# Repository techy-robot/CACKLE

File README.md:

---
modified: 2025-11-08T10:36:11-07:00
---
# CACKLE - Card Adaptable Controller Kinetic Link Electronics

This is designed to be a super small, open source, adaptable control board. Each module is arranged in units of 1.5cm squared, but can handle high power micro robotic actuators, such as my [Mighty-Micro-Motors](https://github.com/techy-robot/Mighty-Micro-Motors). Ideally this board can be reused and rebuilt for all sorts of small robots.

You can read up on specific modules in their respective git sub modules in Hardware, or take a look at the overall architecture

Real Life pictures:

3D model demo:

# Architecture
There are currently 6 types of sub-boards:
- Hubs (with a MCU on it, supports 2 or 4 drivers, 2 expansion cards, and a chain of peers)
- PSUs (typically only one board)
- Expansion Cards (vertical mezzanine connector boards for breaking out sensors and other interfaces)
- Drivers (Any high power driver)
- nanoSPI devices (Small 7-pin flex cable SPI devices, mostly for sensors)
- Passives (spacers, end caps, etc...)

The base unit for this project is 1.5 cm squared. The expansion cards and drivers should each be 1 unit, the Hubs 1x1 or 1x2, and the PSUs 3x1 units. For example, with a 12 motor board you would need 1 PSU, 3 1-by-2 hubs, and 12 drivers; the board would be 45x105mm. nanoSPI devices can be much smaller due to the  2.4mm wide flex cable, such as a 5mm diameter magnetic encoder.

Unfortunately I was unable to create a 45x15mm PSU for the first version, it had to be extended up by 5mm to fit the high current circuitry.

My initial idea was to have spring contacts to allow easy clip in clip out, but finding no connectors quite what I wanted and unable to manufacture my own, I went with 1.27mm pitch pin headers and micro Keystone edge board connectors for power.

Original (bit outdated) sketch of the architecture:

# Goals
- Adaptable 
- Small
- Extendable by other developers
- Easy to use
- Powerful

# Features
## Required:
- Super Small modules
- Hubs with an mcu that can talk to its peers and a master
- Motor driver boards that can handle several amps
- Sensor ports with protocols like i2c and SPI
- Extendable architecture
- PSUs
- LED status lights

## Nice to Have
- Distributed computing with a multi-master network
- Easy automatic hardware configuration
- Ability to stack hubs vertically using the Expansion Card system, in addition to horizontal chaining.

# Software
As of now software is very limited in scope, I have not had the time to fully assembly and test the boards I have made. I am planning on using SimpleFOC and Luos Engine. SimpleFOC is a motor driver library for Field Oreinted Control for motors. Luos Engine is a lightweight-distributed communication engine that aims to make hardware as modular as software. Combined, I have covered 50% of the use-cases of the code necessary for this project.

See [Software](Software/README.md) for more.

# Contributing
Feal free to contribute in any way possible! This is an open-source project, and with so many modules yet to be explored, I encourage you to help test boards, create modules or code, or ask about the project!

- GitHub Discussions: Participate in discussions on GitHub to share your experiences and ask questions.
- Contribute: Help develop the project, create PRs with new features or modules
- Report: Open issues, give me feedback!

Read the Architecture notes and [CONTRIBUTING.md](CONTRIBUTING.md) for more in-depth on this.

# A Note on Project Management
I am using Obsidian.md as my notetaking and documentation tool. A lot of the markdown files you will see in this repo might look a bit weird; that is due to the YAML file front-matter that Obsidian supports, and occasional plugins with custom code.

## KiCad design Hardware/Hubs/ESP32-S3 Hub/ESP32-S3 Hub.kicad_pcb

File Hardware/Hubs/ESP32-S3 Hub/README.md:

---
modified: 2025-01-12T16:18:18-07:00
---

# ESP32-S3 Hub

This is a 4-driver hub based on the Espressif ESP32-S3FH4 chip. It has two cores powerful running at 240 mhz, and 4mb of flash memory. Other variants of the ESP32-S3 can be used as long as they have built in flash memory.

The ESP32-S3 chip does not *quite* have enough pins for driving 4 motors and several sensors, so some cuts were made. For example, on all 4 ports for the ADCs, only two out of three pins are actually connected. This will work for brushed and brushless FOC control, but it may not work for other use cases. I also had to use the USB lines for a tri-state shift register, which controls all the SPI chip select lines. I am planning on programming the chip via UART, which means that the RS485 lines must be disconnected.

The SPI bus should be able to operate at 80mhz, though this has not been tested yet. For all practical use-cases I am limiting this to 20mhz.

Partial 3D picture (headers not shown)

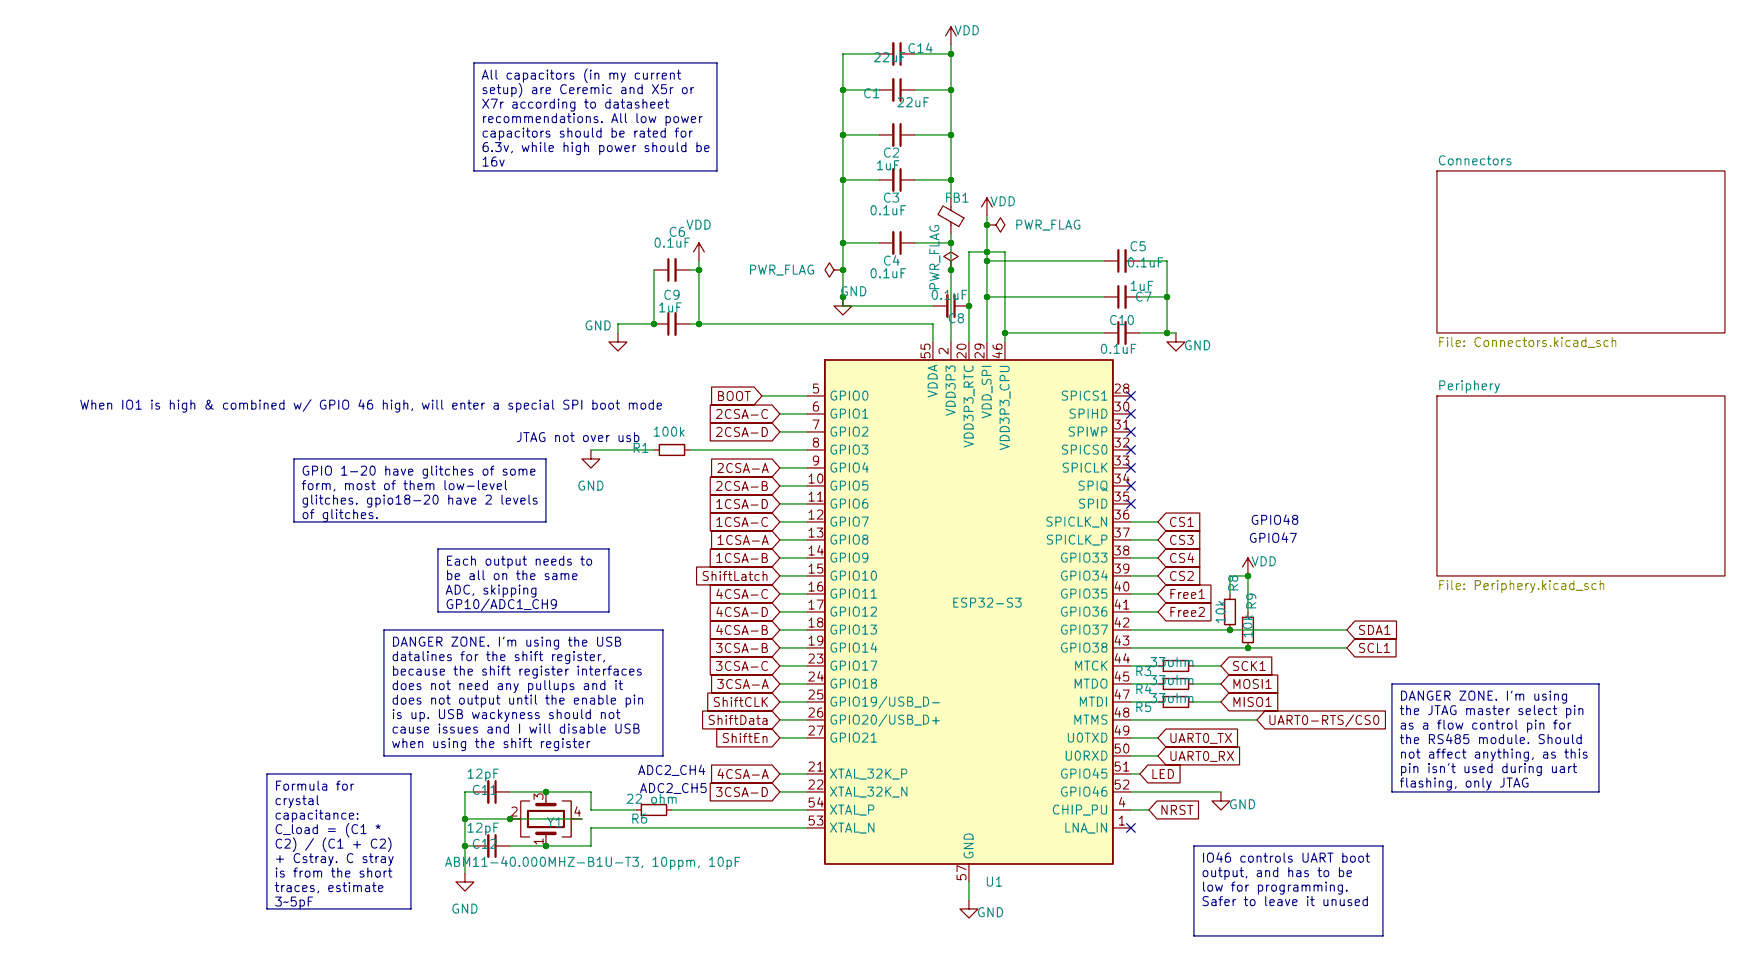
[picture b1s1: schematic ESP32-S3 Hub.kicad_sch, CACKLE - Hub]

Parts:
C1, C14: 22uF; C_0402_1005Metric; LCSC C415703
C2, C7, C9: 1uF; C_0402_1005Metric; LCSC C52923
C3, C4, C5, C6, C8, C10: 0.1uF; C_0402_1005Metric; LCSC C1525
C11, C12: 12pF; C_0402_1005Metric; LCSC C1547
FB1: 120ohm imp @100mhz, 1 amp; L_0402_1005Metric; LCSC C82861
R1: 100k; R_0402_1005Metric; LCSC C25741
R3, R4, R5: 33ohm; R_0402_1005Metric; LCSC C25105
R6: 22 ohm; R_0402_1005Metric; LCSC C25092
R8, R9: 10k; R_0402_1005Metric; LCSC C25744
U1: ESP32-S3; QFN-56-1EP_7x7mm_P0.4mm_EP4x4mm; LCSC C3013940
Y1: ABM11-40.000MHZ-B1U-T3, 10ppm, 10pF; Crystal_SMD_2016-4Pin_2.0x1.6mm; LCSC C648973

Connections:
1CSA-A: U1.13 (GPIO8); also elsewhere on the board
1CSA-B: U1.14 (GPIO9); also elsewhere on the board
1CSA-C: U1.12 (GPIO7); also elsewhere on the board
1CSA-D: U1.11 (GPIO6); also elsewhere on the board
2CSA-A: U1.9 (GPIO4); also elsewhere on the board
2CSA-B: U1.10 (GPIO5); also elsewhere on the board
2CSA-C: U1.6 (GPIO1); also elsewhere on the board
2CSA-D: U1.7 (GPIO2); also elsewhere on the board
3CSA-A: U1.24 (GPIO18); also elsewhere on the board
3CSA-B: U1.19 (GPIO14); also elsewhere on the board
3CSA-C: U1.23 (GPIO17); also elsewhere on the board
3CSA-D: U1.22 (XTAL_32K_N); also elsewhere on the board
4CSA-A: U1.21 (XTAL_32K_P); also elsewhere on the board
4CSA-B: U1.18 (GPIO13); also elsewhere on the board
4CSA-C: U1.16 (GPIO11); also elsewhere on the board
4CSA-D: U1.17 (GPIO12); also elsewhere on the board
BOOT: U1.5 (GPIO0); also elsewhere on the board
CS1: U1.36 (SPICLK_N); also elsewhere on the board
CS2: U1.39 (GPIO34); also elsewhere on the board
CS3: U1.37 (SPICLK_P); also elsewhere on the board
CS4: U1.38 (GPIO33); also elsewhere on the board
Free1: U1.40 (GPIO35); also elsewhere on the board
Free2: U1.41 (GPIO36); also elsewhere on the board
GND: C1.2, C2.2, C3.2, C4.2, C5.2, C6.1, C7.2, C8.2, C9.1, C10.2, C11.2, C12.2, C14.2, R1.2, U1.52 (GPIO46), U1.57 (GND), Y1.2, Y1.4; also elsewhere on the board
LED: U1.51 (GPIO45); also elsewhere on the board
MISO1: R5.2; also elsewhere on the board
MOSI1: R4.2; also elsewhere on the board
NRST: U1.4 (CHIP_PU); also elsewhere on the board
unnamed: C4.1, FB1.1, U1.2 (VDD3P3), U1.3 (VDD3P3)
unnamed: C11.1, R6.1, Y1.3
unnamed: R1.1, U1.8 (GPIO3)
unnamed: R3.1, U1.44 (MTCK)
unnamed: R5.1, U1.47 (MTDI)
unnamed: R4.1, U1.45 (MTDO)
unnamed: C12.1, U1.53 (XTAL_N), Y1.1
unnamed: R6.2, U1.54 (XTAL_P)
SCK1: R3.2; also elsewhere on the board
SCL1: R9.2, U1.43 (GPIO38); also elsewhere on the board
SDA1: R8.2, U1.42 (GPIO37); also elsewhere on the board
ShiftCLK: U1.25 (GPIO19/USB_D-); also elsewhere on the board
ShiftData: U1.26 (GPIO20/USB_D+); also elsewhere on the board
ShiftEn: U1.27 (GPIO21); also elsewhere on the board
ShiftLatch: U1.15 (GPIO10); also elsewhere on the board
UART0-RTS/CS0: U1.48 (MTMS); also elsewhere on the board
UART0_RX: U1.50 (U0RXD); also elsewhere on the board
UART0_TX: U1.49 (U0TXD); also elsewhere on the board
VDD: C1.1, C2.1, C3.1, C5.1, C6.2, C7.1, C8.1, C9.2, C10.1, C14.1, FB1.2, R8.1, R9.1, U1.20 (VDD3P3_RTC), U1.29 (VDD_SPI), U1.46 (VDD3P3_CPU), U1.55 (VDDA), U1.56 (VDDA); also elsewhere on the board

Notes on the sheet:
GPIO48
JTAG not over usb
GPIO47
When IO1 is high & combined w/ GPIO 46 high, will enter a special SPI boot mode
ADC2_CH4
ADC2_CH5
DANGER ZONE. I'm using the JTAG master select pin as a flow control pin for the RS485 module. Should not affect anything, as this pin isn't used during uart flashing, only JTAG
DANGER ZONE. I'm using the USB datalines for the shift register, because the shift register interfaces does not need any pullups and it does not output until the enable pin is up. USB wackyness should not cause issues and I will disable USB when using the shift register
All capacitors (in my current setup) are Ceremic and X5r or X7r according to datasheet recommendations. All low power capacitors should be rated for 6.3v, while high power should be 16v
IO46 controls UART boot output, and has to be low for programming. Safer to leave it unused
Each output needs to be all on the same ADC, skipping GP10/ADC1_CH9
GPIO 1-20 have glitches of some form, most of them low-level glitches. gpio18-20 have 2 levels of glitches.
Formula for crystal capacitance: C_load = (C1 * C2) / (C1 + C2) + Cstray. C stray is from the short traces, estimate 3~5pF

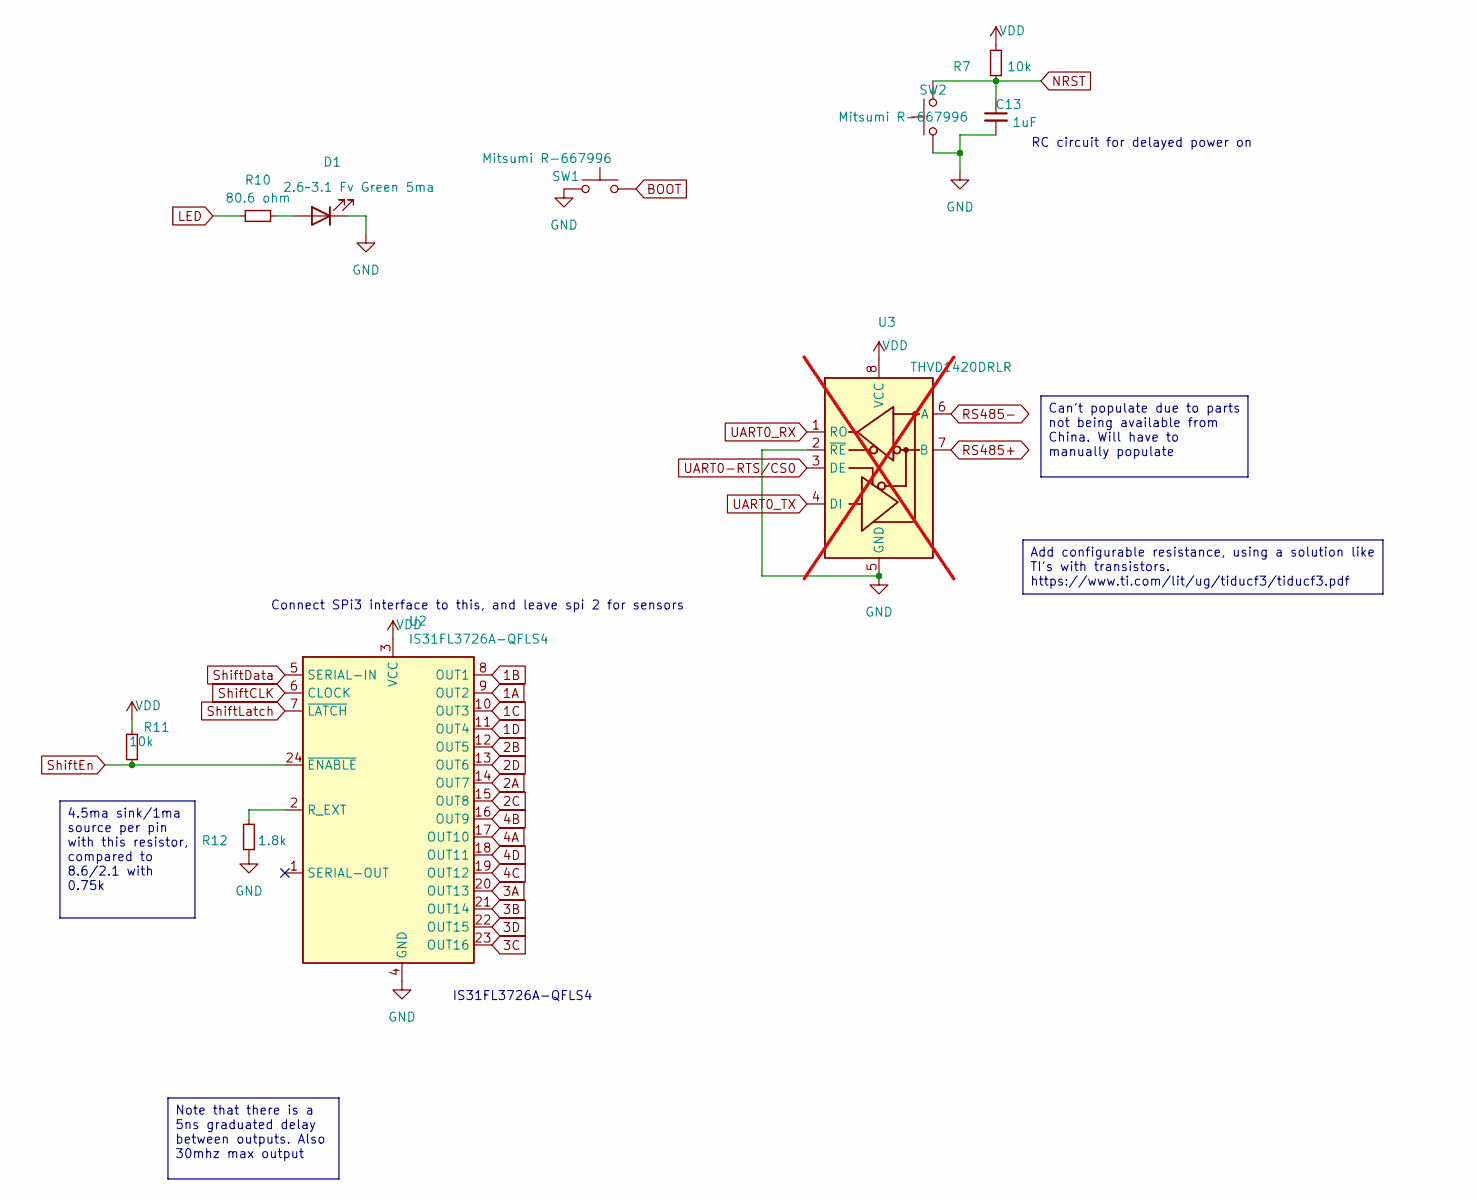
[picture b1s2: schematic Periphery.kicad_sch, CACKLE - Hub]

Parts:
C13: 1uF; C_0402_1005Metric; LCSC C52923
D1: 2.6~3.1 Fv Green 5ma; LED_0603_1608Metric_Pad1.05x0.95mm_HandSolder; LCSC C3028858
R7, R11: 10k; R_0402_1005Metric; LCSC C25744
R10: 80.6 ohm; R_0402_1005Metric; LCSC C185392
R12: 1.8k; R_0402_1005Metric; LCSC C25744
SW1, SW2: Mitsumi R-667996; R-667995_MIT; LCSC C4365007
U2: IS31FL3726A-QFLS4; QFN-24-1EP_4x4mm_P0.5mm_EP2.7x2.7mm
U3: THVD1420DRLR; SOT-583-8; not fitted

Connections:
1A: U2.9 (OUT2); also elsewhere on the board
1B: U2.8 (OUT1); also elsewhere on the board
1C: U2.10 (OUT3); also elsewhere on the board
1D: U2.11 (OUT4); also elsewhere on the board
2A: U2.14 (OUT7); also elsewhere on the board
2B: U2.12 (OUT5); also elsewhere on the board
2C: U2.15 (OUT8); also elsewhere on the board
2D: U2.13 (OUT6); also elsewhere on the board
3A: U2.20 (OUT13); also elsewhere on the board
3B: U2.21 (OUT14); also elsewhere on the board
3C: U2.23 (OUT16); also elsewhere on the board
3D: U2.22 (OUT15); also elsewhere on the board
4A: U2.17 (OUT10); also elsewhere on the board
4B: U2.16 (OUT9); also elsewhere on the board
4C: U2.19 (OUT12); also elsewhere on the board
4D: U2.18 (OUT11); also elsewhere on the board
BOOT: SW1.2; also elsewhere on the board
GND: C13.2, D1.1 (K), R12.1, SW1.1, SW2.1, U2.4 (GND), U2.25 (GND), U3.2 (~RE), U3.5 (GND); also elsewhere on the board
LED: R10.1; also elsewhere on the board
NRST: C13.1, R7.1, SW2.2; also elsewhere on the board
unnamed: D1.2 (A), R10.2
unnamed: R12.2, U2.2 (R_EXT)
RS485+: U3.7 (B); also elsewhere on the board
RS485-: U3.6 (A); also elsewhere on the board
ShiftCLK: U2.6 (CLOCK); also elsewhere on the board
ShiftData: U2.5 (SERIAL-IN); also elsewhere on the board
ShiftEn: R11.1, U2.24 (~ENABLE); also elsewhere on the board
ShiftLatch: U2.7 (~LATCH); also elsewhere on the board
UART0-RTS/CS0: U3.3 (DE); also elsewhere on the board
UART0_RX: U3.1 (RO); also elsewhere on the board
UART0_TX: U3.4 (DI); also elsewhere on the board
VDD: R7.2, R11.2, U2.3 (VCC), U3.8 (VCC); also elsewhere on the board

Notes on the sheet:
IS31FL3726A-QFLS4
RC circuit for delayed power on
Connect SPi3 interface to this, and leave spi 2 for sensors
Can't populate due to parts not being available from China. Will have to manually populate
Add configurable resistance, using a solution like TI's with transistors. https://www.ti.com/lit/ug/tiducf3/tiducf3.pdf
Note that there is a 5ns graduated delay between outputs. Also 30mhz max output
4.5ma sink/1ma source per pin with this resistor, compared to 8.6/2.1 with 0.75k

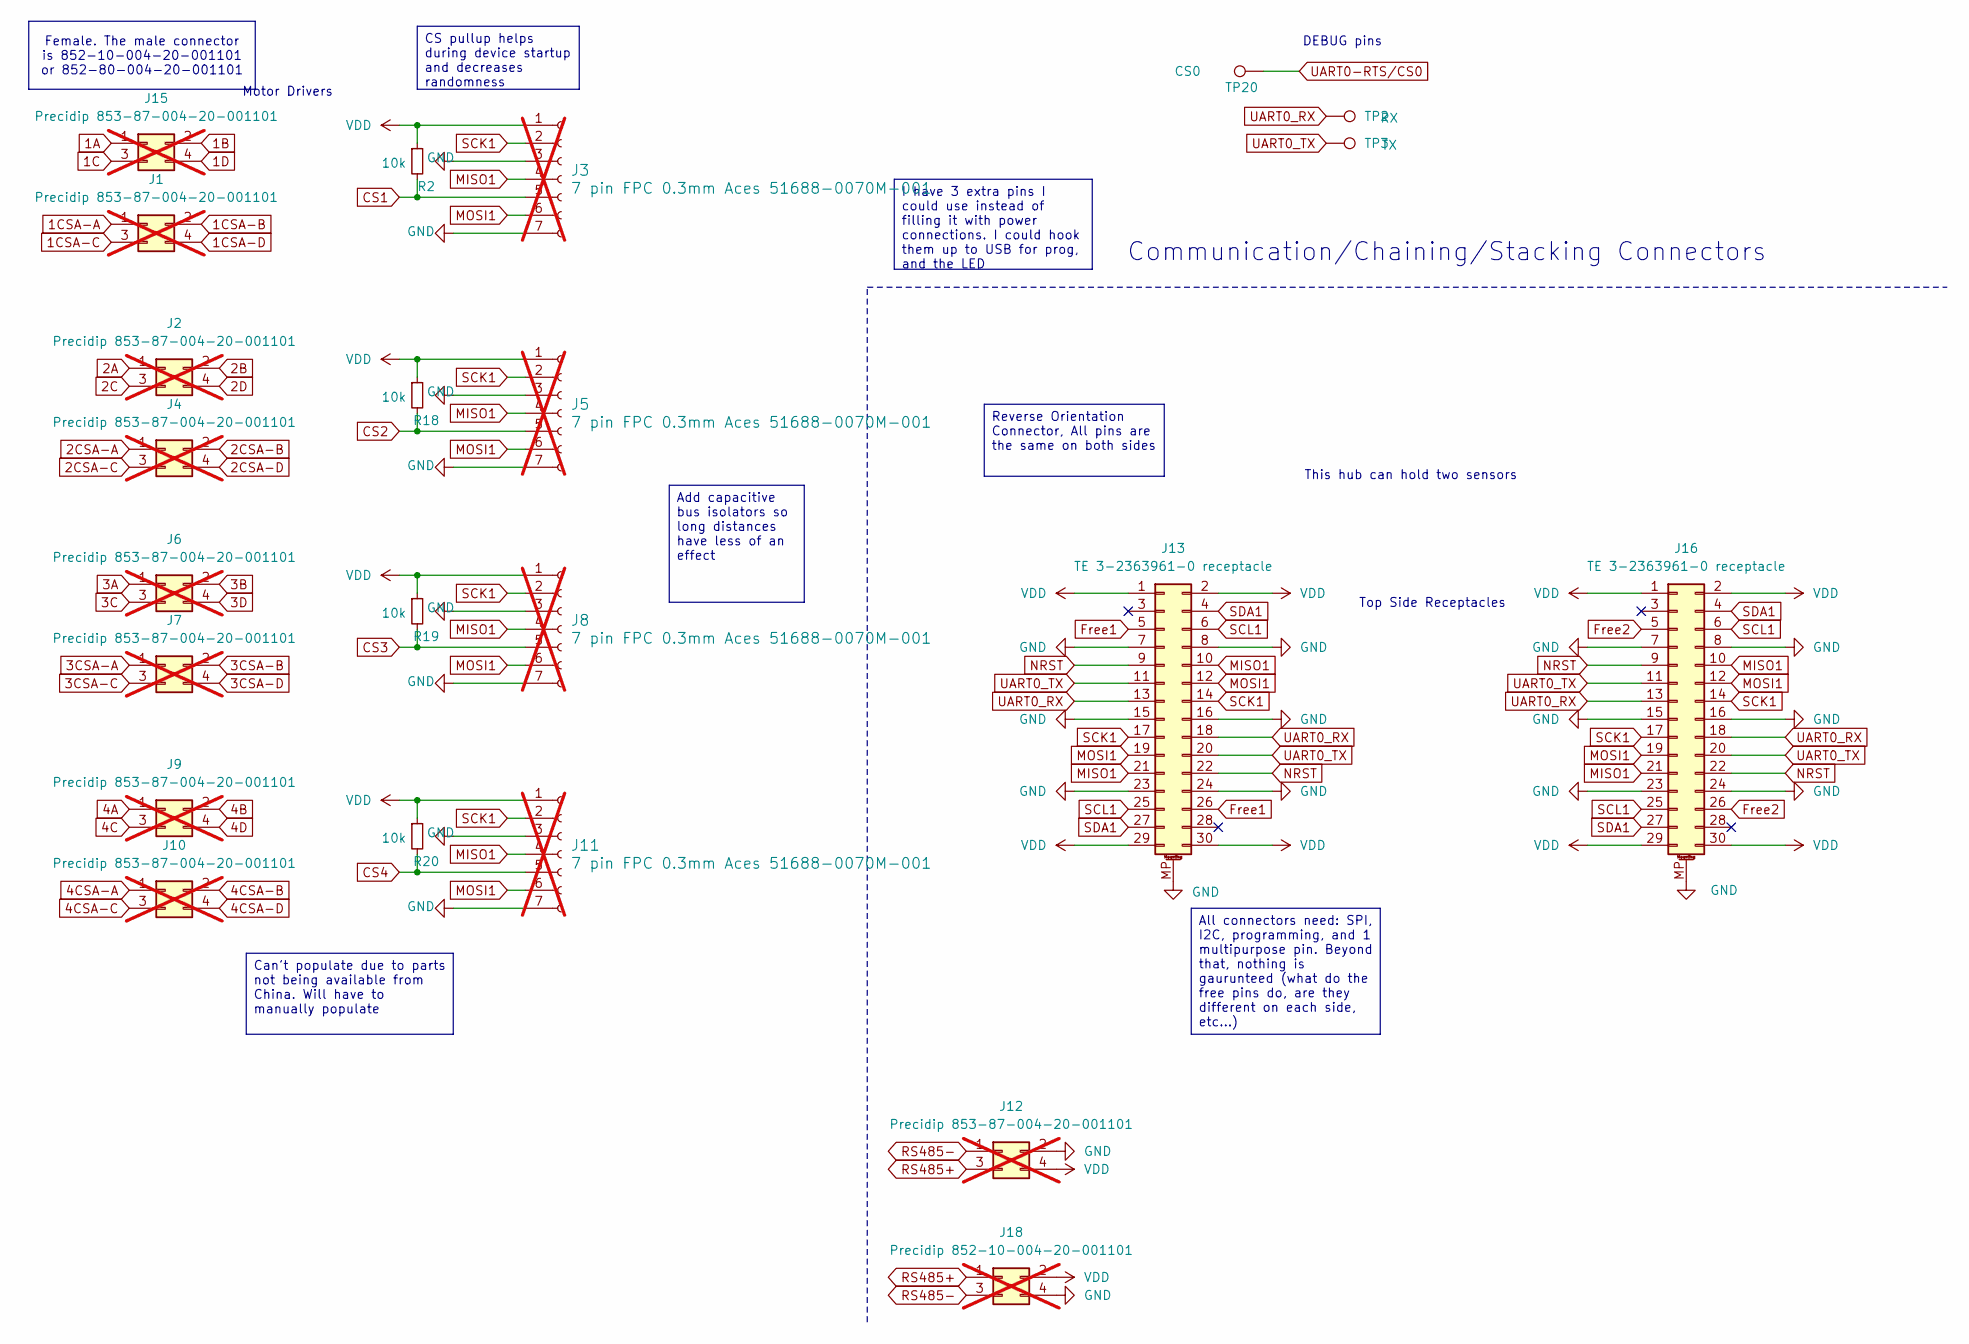
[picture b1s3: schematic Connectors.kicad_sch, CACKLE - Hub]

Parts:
J1, J2, J4, J6, J7, J9, J10, J12, J15: Precidip 853-87-004-20-001101; PinHeader_2x02_P1.27mm_Horizontal; not fitted
J3, J5, J8, J11: 7 pin FPC 0.3mm Aces 51688-0070M-001; fpc_7pin_0.3mm_connector Aces; not fitted
J13, J16: TE 3-2363961-0 receptacle; TE_mezzanine_rec_3-2363961-0; LCSC C425103
J18: Precidip 852-10-004-20-001101; PinHeader_2x02_P1.27mm_Horizontal; not fitted
R2, R18, R19, R20: 10k; R_0402_1005Metric; LCSC C25744
TP2: RX; TestPoint_Pad_D1.0mm
TP3: TX; TestPoint_Pad_D1.0mm
TP20: CS0; TestPoint_Pad_D1.0mm

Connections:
1A: J15.1; also elsewhere on the board
1B: J15.2; also elsewhere on the board
1C: J15.3; also elsewhere on the board
1CSA-A: J1.1; also elsewhere on the board
1CSA-B: J1.2; also elsewhere on the board
1CSA-C: J1.3; also elsewhere on the board
1CSA-D: J1.4; also elsewhere on the board
1D: J15.4; also elsewhere on the board
2A: J2.1; also elsewhere on the board
2B: J2.2; also elsewhere on the board
2C: J2.3; also elsewhere on the board
2CSA-A: J4.1; also elsewhere on the board
2CSA-B: J4.2; also elsewhere on the board
2CSA-C: J4.3; also elsewhere on the board
2CSA-D: J4.4; also elsewhere on the board
2D: J2.4; also elsewhere on the board
3A: J6.1; also elsewhere on the board
3B: J6.2; also elsewhere on the board
3C: J6.3; also elsewhere on the board
3CSA-A: J7.1; also elsewhere on the board
3CSA-B: J7.2; also elsewhere on the board
3CSA-C: J7.3; also elsewhere on the board
3CSA-D: J7.4; also elsewhere on the board
3D: J6.4; also elsewhere on the board
4A: J9.1; also elsewhere on the board
4B: J9.2; also elsewhere on the board
4C: J9.3; also elsewhere on the board
4CSA-A: J10.1; also elsewhere on the board
4CSA-B: J10.2; also elsewhere on the board
4CSA-C: J10.3; also elsewhere on the board
4CSA-D: J10.4; also elsewhere on the board
4D: J9.4; also elsewhere on the board
CS1: J3.5, R2.2; also elsewhere on the board
CS2: J5.5, R18.2; also elsewhere on the board
CS3: J8.5, R19.2; also elsewhere on the board
CS4: J11.5, R20.2; also elsewhere on the board
Free1: J13.5, J13.26; also elsewhere on the board
Free2: J16.5, J16.26; also elsewhere on the board
GND: J3.3, J3.7, J5.3, J5.7, J8.3, J8.7, J11.3, J11.7, J12.2, J13.7, J13.8, J13.15, J13.16, J13.23, J13.24, J13.MP (MountPin), J16.7, J16.8, J16.15, J16.16, J16.23, J16.24, J16.MP (MountPin), J18.4; also elsewhere on the board
MISO1: J3.4, J5.4, J8.4, J11.4, J13.10, J13.21, J16.10, J16.21; also elsewhere on the board
MOSI1: J3.6, J5.6, J8.6, J11.6, J13.12, J13.19, J16.12, J16.19; also elsewhere on the board
NRST: J13.9, J13.22, J16.9, J16.22; also elsewhere on the board
RS485+: J12.3, J18.1; also elsewhere on the board
RS485-: J12.1, J18.3; also elsewhere on the board
SCK1: J3.2, J5.2, J8.2, J11.2, J13.14, J13.17, J16.14, J16.17; also elsewhere on the board
SCL1: J13.6, J13.25, J16.6, J16.25; also elsewhere on the board
SDA1: J13.4, J13.27, J16.4, J16.27; also elsewhere on the board
UART0-RTS/CS0: TP20.1; also elsewhere on the board
UART0_RX: J13.13, J13.18, J16.13, J16.18, TP2.1; also elsewhere on the board
UART0_TX: J13.11, J13.20, J16.11, J16.20, TP3.1; also elsewhere on the board
VDD: J3.1, J5.1, J8.1, J11.1, J12.4, J13.1, J13.2, J13.29, J13.30, J16.1, J16.2, J16.29, J16.30, J18.2, R2.1, R18.1, R19.1, R20.1; also elsewhere on the board

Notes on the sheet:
Communication/Chaining/Stacking Connectors
Top Side Receptacles
Motor Drivers
This hub can hold two sensors
DEBUG pins
Reverse Orientation Connector, All pins are the same on both sides
CS pullup helps during device startup and decreases randomness
Can't populate due to parts not being available from China. Will have to manually populate
Add capacitive bus isolators so long distances have less of an effect
I have 3 extra pins I could use instead of filling it with power connections. I could hook them up to USB for prog, and the LED
All connectors need: SPI, I2C, programming, and 1 multipurpose pin. Beyond that, nothing is gaurunteed (what do the free pins do, are they different on each side, etc...)
Female. The male connector is 852-10-004-20-001101 or 852-80-004-20-001101

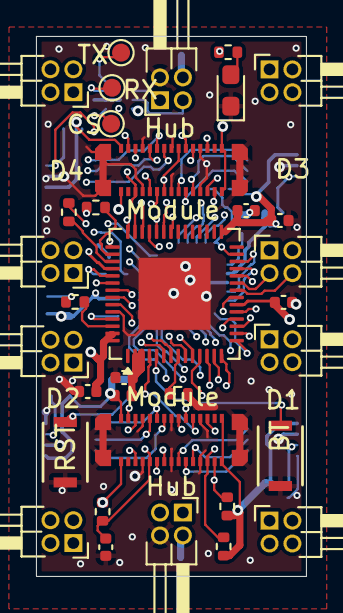
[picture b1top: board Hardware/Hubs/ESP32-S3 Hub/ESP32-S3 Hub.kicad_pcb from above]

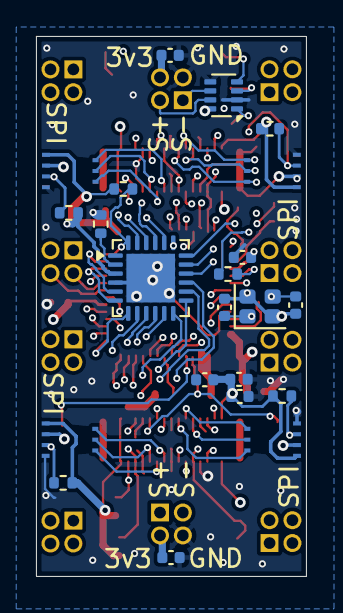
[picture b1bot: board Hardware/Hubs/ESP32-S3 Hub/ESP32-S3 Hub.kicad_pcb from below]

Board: 6 copper layers, 15.0 x 30.0 mm, 56 parts (22 on the bottom side), 67 nets.

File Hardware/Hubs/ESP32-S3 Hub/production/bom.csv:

Designator,Footprint,Quantity,Value,LCSC Part #
"C1, C14",0402,2,22uF,C415703
"C10, C3, C4, C5, C6, C8",0402,6,0.1uF,C1525
"C11, C12",0402,2,12pF,C1547
"C13, C2, C7, C9",0402,4,1uF,C52923
D1,0603,1,2.6~3.1 Fv Green 5ma,C3028858
FB1,0402,1,"120ohm imp @100mhz, 1 amp",C82861
"J13, J16",TE_mezzanine_rec_3-2363961-0,2,TE 3-2363961-0 receptacle,C425103
"J14, J17",TE_mezzanine_conn_3-2363962-0,2,TE 3-2363962-0 Connector,C425104
R1,0402,1,100k,C25741
R10,0402,1,80.6 ohm,C185392
"R11, R18, R19, R2, R20, R7, R8, R9",0402,8,10k,C25744
"R3, R4, R5",0402,3,33ohm,C25105
R6,0402,1,22 ohm,C25092
"SW1, SW2",R-667995_MIT,2,Mitsumi R-667996,C4365007
U1,QFN-56-1EP_7x7mm_P0.4mm_EP4x4mm,1,ESP32-S3,C3013940
U2,DHVQFN-16-1EP_2.5x3.5mm_P0.5mm_EP1x2mm,1,74HC595,C730243
Y1,Crystal_SMD_2016-4Pin_2.0x1.6mm,1,"ABM11-40.000MHZ-B1U-T3, 10ppm, 10pF",C648973

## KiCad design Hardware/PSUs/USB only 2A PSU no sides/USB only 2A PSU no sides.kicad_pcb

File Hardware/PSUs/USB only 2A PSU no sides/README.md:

---
modified: 2025-09-09T20:54:29-06:00
---

# USB Only PSU no sides

The main ICs are an mcu, and a 5v 2a switching regulator. The system can theoretically handle 20 volt spikes, but this is mostly meant for 5v output on one side only.

The MCU has several purposes:
- Manage USB-C PD negotiations over the CC pins (built in PHY)
- Report voltage & current sensor data over the bus
- Act as a host adapter to convert USB or SPI data to rs485 bus commands and back. Helpful for debugging the system via a laptop, or if your main compute board needs to control the motors and sensors and doesn't have RS485 built in.

The CH32X035G8U6 MCU will be swapped from to a STM32G071 x8/xB for sourcing reasons, which also implements usb pd but is a little more expensive. To get a  QFN28/32 chip with USB PD, I need the N version. My options on digikey are STM32G071GBU6N ($2.74) and STM32G071KBU6N ($2.94)

Also looking for USB C connectors on [DigiKey](https://www.digikey.com/en/products/filter/usb-dvi-hdmi-connector-assemblies/312?s=N4IgjCBcoEwOxVAYygMwIYBsDOBTANCAPZQDaIALHAJwBscFIhFMtYArDE5fBWF4Q5hqMaiAC6hAA4AXKCADKMgE4BLAHYBzEAF9CMAByIQKSBhwFiZSmAMBmauwnS5kRSo3a9IUcdPm8QhJIcgdRWgAGZxBZeSU1LV1CAFouaBMoFQBXS2DyJ3EdbzTyLOwAIwACFEkQWmNVABN5ZLAIiBd5bhkATylceXRsFCKgA).

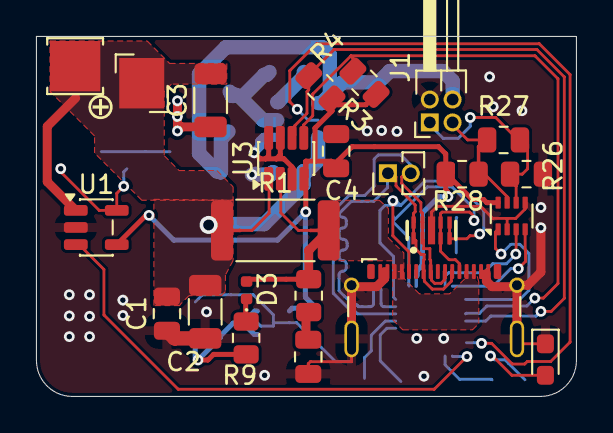
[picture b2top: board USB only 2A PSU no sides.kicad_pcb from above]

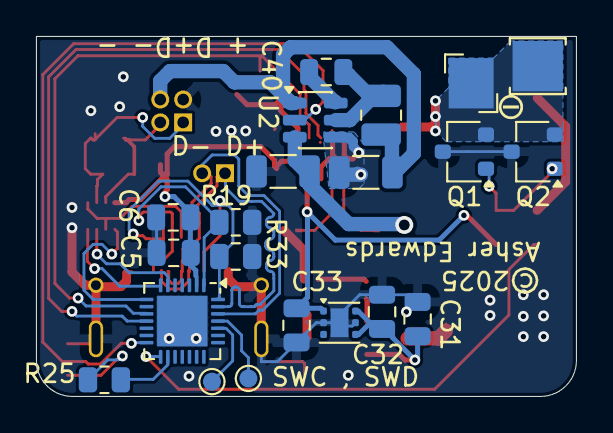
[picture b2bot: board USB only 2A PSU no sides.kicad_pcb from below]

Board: 2 copper layers, 30.0 x 20.0 mm, 48 parts (21 on the bottom side), 32 nets.

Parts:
C1, C7, C31: 10uF, 16v; C_0805_2012Metric
C2, C3, C27, C28: 22uf, 16v CL31A226MOCLNN; C_1206_3216Metric
C4, C5, C32, C40: 100nF, 16v; C_0805_2012Metric
C6: 4.7uF, 16v; C_0805_2012Metric
C33: 2.2uF, 16v; C_0805_2012Metric
D3: GSDH3005; D_0402_1005Metric
D4: 2.6~3.1 Fv Green 5ma; LED_0603_1608Metric_Pad1.05x0.95mm_HandSolder
D11: CDDFN10-3324P; CDDFN103324P
J1: Precidip 853-87-004-20-001101; PinHeader_2x02_P1.27mm_Horizontal
J3, J7: Keystone 3579; Keystone_3579
J5, J9: Keystone 3569; Keystone_3569_half
J10: G-Switch-GT-USB-7025; USB_C_G-Switch_GT-USB-7025-JLCPCBv
J12: USB; PinHeader_1x02_P1.27mm_Vertical
L3: 2.2uH, WIP322512A-2R2MLDG; L_1008_2520Metric
NT1, NT2: NetTie_2; NetTie-2_SMD_Pad0.2mm
NT12: PWR NetTie; NetTie-2_SMD_Pad0.28mm
Q1, Q2: PJA3430, or HL 2320A; SC-59
R1: 50mOhm; R_2512_6332Metric
R2: 2ohm; R_0805_2012Metric
R3, R4: 10k; R_0805_2012Metric
R9: 10ohm; R_0805_2012Metric
R19, R33: 5.1k; R_0805_2012Metric
R25: 80.6 ohm; R_0805_2012Metric
R26, R27, R28: 120 ohm; R_0805_2012Metric
TP1: SWD; TestPoint_Pad_D1.0mm
TP2: SWC; TestPoint_Pad_D1.0mm
U1: FAN3111E; SOT-23-5
U2: AP63203WU; TSOT-23-6
U3: INA219AxDCN; SOT-23-8
U4: CH32X035G8U6; QFN-28-1EP_4x4mm_P0.4mm_EP2.8x2.8mm
U5: THVD1420DRLR; SOT-583-8
U7: TPS7A2633DRV; WSON-6-1EP_2x2mm_P0.65mm_EP1x1.6mm

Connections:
/Connectors/3.3v: C27.1, J1.4, L3.2, U2.1 (FB)
/Connectors/CC1: D11.5 (IN/OUT_4), D11.6 (NC_1), J10.A5 (CC1), R33.2, U4.28 (CC1/PC14)
/Connectors/CC2: D11.4 (IN/OUT_3), D11.7 (NC_2), J10.B5 (CC2), R19.2, U4.1 (CC2/PC15)
/Connectors/D+: D11.1 (IN/OUT_1), D11.10 (NC_4), J10.A6 (D+), J10.B6 (D+), J12.1, U4.27 (USB1_DP/PC17)
/Connectors/D-: D11.2 (IN/OUT_2), D11.9 (NC_3), J10.A7 (D-), J10.B7 (D-), J12.2, U4.26 (USB1_DM/PC16)
/Connectors/RS485+: J1.3, R27.2, R28.2, U5.7 (B)
/Connectors/RS485-: J1.1, R26.1, R27.1, U5.6 (A)
/Connectors/USBPWR: J10.A4 (VBUS), J10.A9 (VBUS), J10.B4 (VBUS), J10.B9 (VBUS), NT2.2, NT12.2, R1.2, R2.2
/MCU/3.3v: C4.2, C5.1, C6.1, C33.1, R3.2, R4.2, R28.1, U1.4 (XREF), U3.4 (VS), U4.2 (VDD), U5.8 (VCC), U7.1 (OUT)
/MCU/3v3 EN: U2.2 (EN), U4.14 (PB3)
/MCU/5v EN: U1.3 (IN+), U4.15 (PB4)
/MCU/LED: R25.1, U4.16 (PB1/PB5/ADC9)
/MCU/UART1-RTS: U4.6 (ADC1/PA1), U5.3 (DE)
/MCU/UART1_RX: U4.8 (ADC3/PA3), U5.1 (RO)
/MCU/UART1_TX: U4.7 (ADC2/PA2), U5.4 (DI)
/PSU/5V Out: C1.2, C2.2, C3.2, C28.1, J3.1, J5.1, NT1.2, R1.1, U1.1 (VDD), U2.3 (IN)
/SCL: R3.1, U3.5 (SCL), U4.10 (ADC5/PA5)
/SDA: R4.1, U3.6 (SDA), U4.11 (ADC6/PA6)
GND: C1.1, C2.1, C4.1, C5.2, C6.2, C7.2, C27.2, C28.2, C31.2, C32.2, C33.2, D4.1 (K), D11.3 (GND_1), D11.8 (GND_2), J1.2, J10.A1 (GND), J10.A12 (GND), J10.B1 (GND), J10.B12 (GND), J10.S1 (SHIELD), Q1.3 (D), Q2.3 (D), R19.1, R26.2, R33.1, U1.2 (GND), U2.4 (GND), U3.3 (GND), U3.7 (A0), U3.8 (A1), U4.29 (GND), U5.2 (~RE), U5.5 (GND), U7.2 (NC), U7.5 (GND), U7.7 (EP)
GNDPWR: C3.1, J7.1, J9.1, Q1.2 (S), Q2.2 (S)
unnamed: C7.1, R2.1
unnamed: D3.2 (A), NT12.1
unnamed: D3.1 (K), R9.2
unnamed: D4.2 (A), R25.2
unnamed: Q1.1 (G), Q2.1 (G), U1.5 (OUT)
unnamed: C40.1, U2.6 (BST)
unnamed: C40.2, L3.1, U2.5 (SW)
unnamed: NT1.1, U3.1 (IN+)
unnamed: NT2.1, U3.2 (IN-)
unnamed: TP2.1, U4.24 (SWCLK/PC19)
unnamed: TP1.1, U4.25 (SWDIO/PC18)
unnamed: C31.1, C32.1, R9.1, U7.4 (EN), U7.6 (IN)

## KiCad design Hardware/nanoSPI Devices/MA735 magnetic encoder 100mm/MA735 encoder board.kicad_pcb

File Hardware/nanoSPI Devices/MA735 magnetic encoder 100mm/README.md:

---
modified: 2025-05-05T16:26:33-07:00
---

# nanoSPI MA735 magnetic encoder

This is a super compact SPI magnetic encoder, with the flex cable being 2.4mm wide and 100mm long, and the tip around 5.6mm diameter. It is quite simple, and supports on shaft or side-shaft mounting with correction.

It supports a max of 25mhz bus speed, though practically speaking this is closer to 20mhz. It supports SPI mode 0 or 3, detecting automatically.

The sensor itself, MagAlpha MA735, has some quirks to it. It is variable resolution ranging from 9 to 13 bit which is inversely proportional to its speed. If you want the max measurement speed at 60k rpm, then you will have to read 9-bit angles. This is all dictated by the Filter Window setting, resolution and speed are derived from this setting.

This can be used as a template for other nanoSPI sensors, or cables.

Also, the connectors for these sensors with a 0.35mm pitch are SUPER finicky to actually solder by hand, reflow is 1000% recommended. You will burn the plastic onto a soldering iron in one swipe.

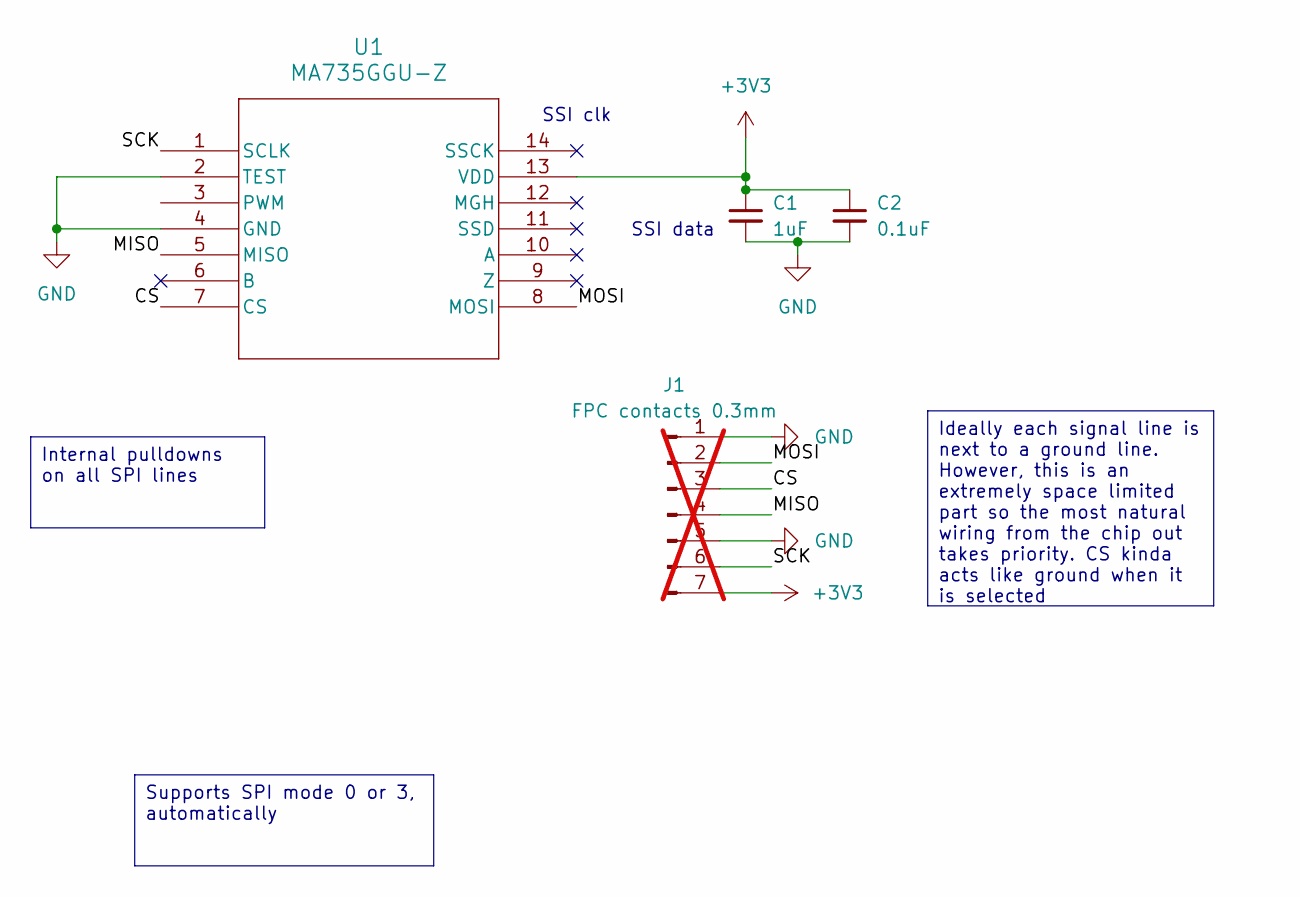
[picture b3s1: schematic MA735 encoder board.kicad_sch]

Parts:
C1: 1uF; C_0402_1005Metric; LCSC C52923
C2: 0.1uF; C_0402_1005Metric; LCSC C1525
J1: FPC contacts 0.3mm; 7pin_fpc_contact_0.3mmptich; not fitted
U1: MA735GGU-Z; UTQFN-14_MA735_MNP; LCSC C17233427

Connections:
+3V3: C1.1, C2.1, J1.7, U1.13 (VDD)
/CS: J1.3, U1.7 (CS)
/MISO: J1.4, U1.5 (MISO)
/MOSI: J1.2, U1.8 (MOSI)
/SCK: J1.6, U1.1 (SCLK)
GND: C1.2, C2.2, J1.1, J1.5, U1.2 (TEST), U1.4 (GND)

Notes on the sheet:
SSI clk
SSI data
Supports SPI mode 0 or 3, automatically
Ideally each signal line is next to a ground line. However, this is an extremely space limited part so the most natural wiring from the chip out takes priority. CS kinda acts like ground when it is selected
Internal pulldowns on all SPI lines

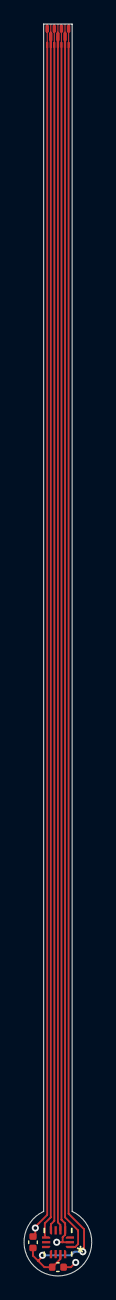
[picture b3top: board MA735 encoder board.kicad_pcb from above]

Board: 2 copper layers, 5.7 x 105.4 mm, 4 parts (0 on the bottom side), 6 nets.

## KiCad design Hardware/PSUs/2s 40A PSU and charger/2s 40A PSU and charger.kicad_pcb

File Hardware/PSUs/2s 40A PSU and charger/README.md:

---
modified: 2025-01-12T19:11:32-07:00
---

# 2s 40A PSU and charger

This is a rather complex power supply unit. It supports USB-C Power Delivery at 9volt 2 amps, and can charge a 2 cell lipo battery. It can pump out 40 amps if the battery supports the current. It also had battery protection and balancing built in, and a RS485 communication unit that can translate USB or SPI data to RS485.

The outer copper is 2oz, and the inner is 0.5 oz. Additional metal is needed to support the full current.

The main ICs on board are the TI BQ24780S battery charger, TI BQ76905 battery balancer and monitor, and a CH32X035G8U6 mcu. The system can theoretically handle 20 volt spikes, but the battery and all down line items could become damaged. I think there is also some 16v capacitors on the power lines that would be damaged. This is really meant for 9v usb-c charging to an 8.4v max lipo.

There are 2 plated through hole pads for the main battery wires, and a JST XH 3-pin connector for the balance plug in the common pin arrangement for Turnigy batteries.

The MCU has several purposes:
- Manage USB-C PD negotiations over the CC pins (built in PHY)
- Interact with the battery charger to keep it alive and change settings for charge profiles and curves
- Trigger battery balancing
- Report battery sensor data over the bus
- Act as a host adapter to convert USB or SPI data to rs485 bus commands and back. Helpful for debugging the system via a laptop, or if your main compute board needs to control the motors and sensors and doesn't have RS485 built in.

Partial 3D image, some connectors missing:

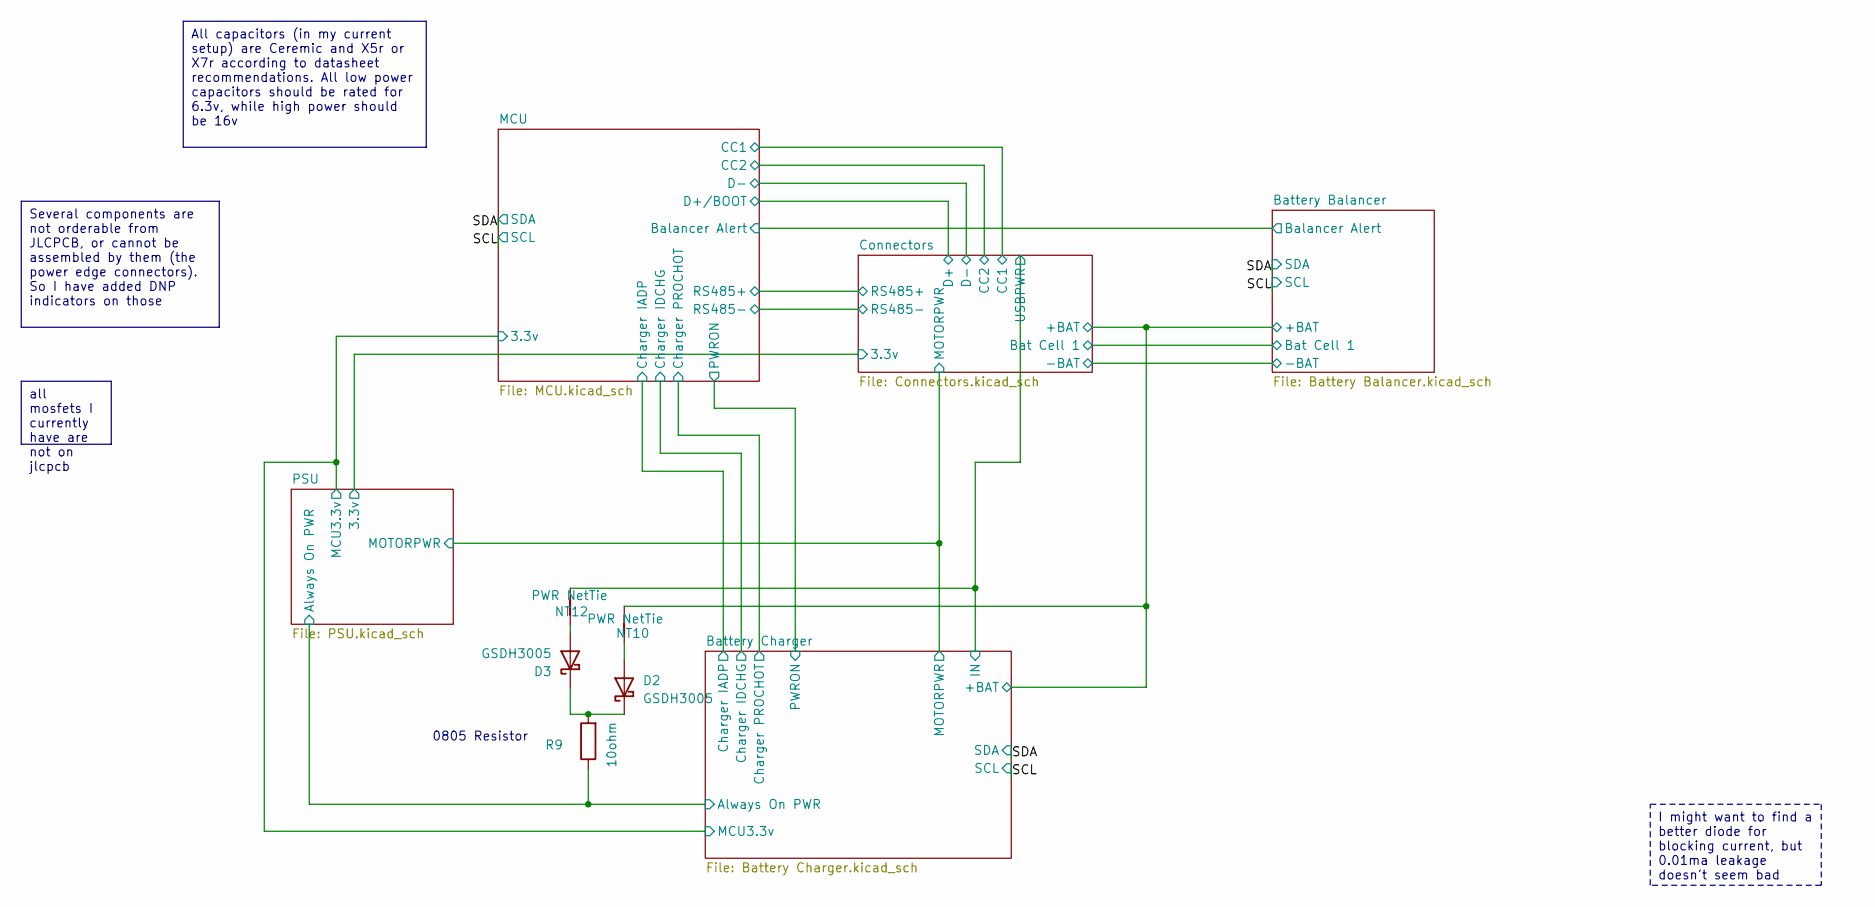
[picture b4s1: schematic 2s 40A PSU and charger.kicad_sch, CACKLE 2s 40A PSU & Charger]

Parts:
D2, D3: GSDH3005; D_0402_1005Metric; LCSC C2837790
NT10, NT12: PWR NetTie; NetTie-2_SMD_Pad0.28mm
R9: 10ohm; R_0805_2012Metric; LCSC C17415

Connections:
/Battery Balancer/+BAT: NT10.2; also elsewhere on the board
/Battery Charger/Always On PWR: R9.1; also elsewhere on the board
/Battery Charger/IN: NT12.2; also elsewhere on the board
unnamed: D2.2 (A), NT10.1
unnamed: D2.1 (K), D3.1 (K), R9.2
unnamed: D3.2 (A), NT12.1

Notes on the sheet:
All capacitors (in my current setup) are Ceremic and X5r or X7r according to datasheet recommendations. All low power capacitors should be rated for 6.3v, while high power should be 16v
Several components are not orderable from JLCPCB, or cannot be assembled by them (the power edge connectors). So I have added DNP indicators on those
all mosfets I currently have are not on jlcpcb
I might want to find a better diode for blocking current, but 0.01ma leakage doesn't seem bad
0805 Resistor

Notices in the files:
Hardware/Hubs/ESP32-S3 Hub/Connectors.kicad_sch:
Licensed under CERN-OHL-S v2
Hardware/PSUs/2s 40A PSU and charger/2s 40A PSU and charger.kicad_pcb:
©2024
Hardware/PSUs/USB only 2A PSU no sides/USB only 2A PSU no sides.kicad_pcb:
©2025
